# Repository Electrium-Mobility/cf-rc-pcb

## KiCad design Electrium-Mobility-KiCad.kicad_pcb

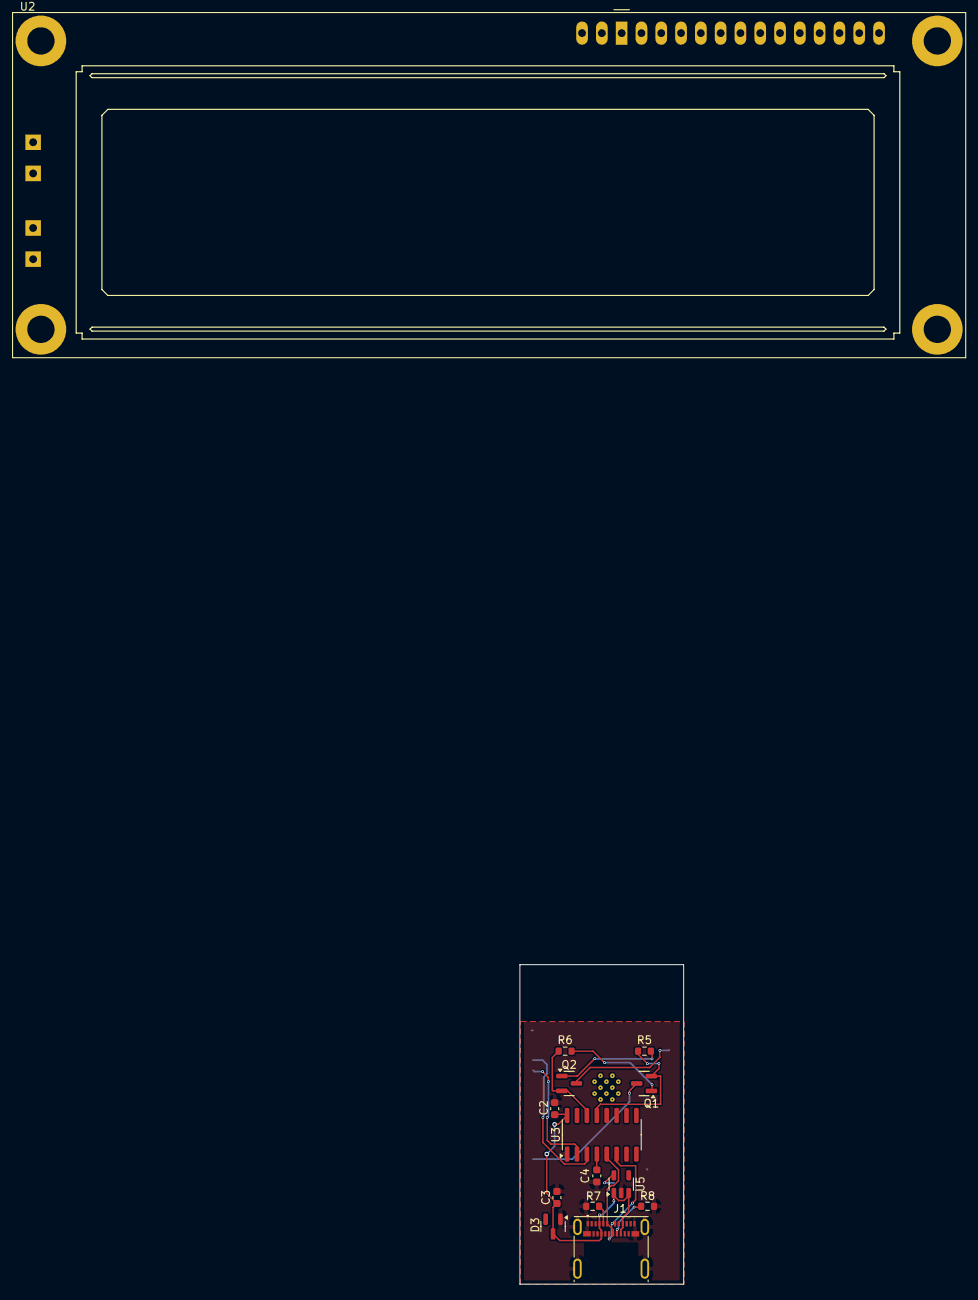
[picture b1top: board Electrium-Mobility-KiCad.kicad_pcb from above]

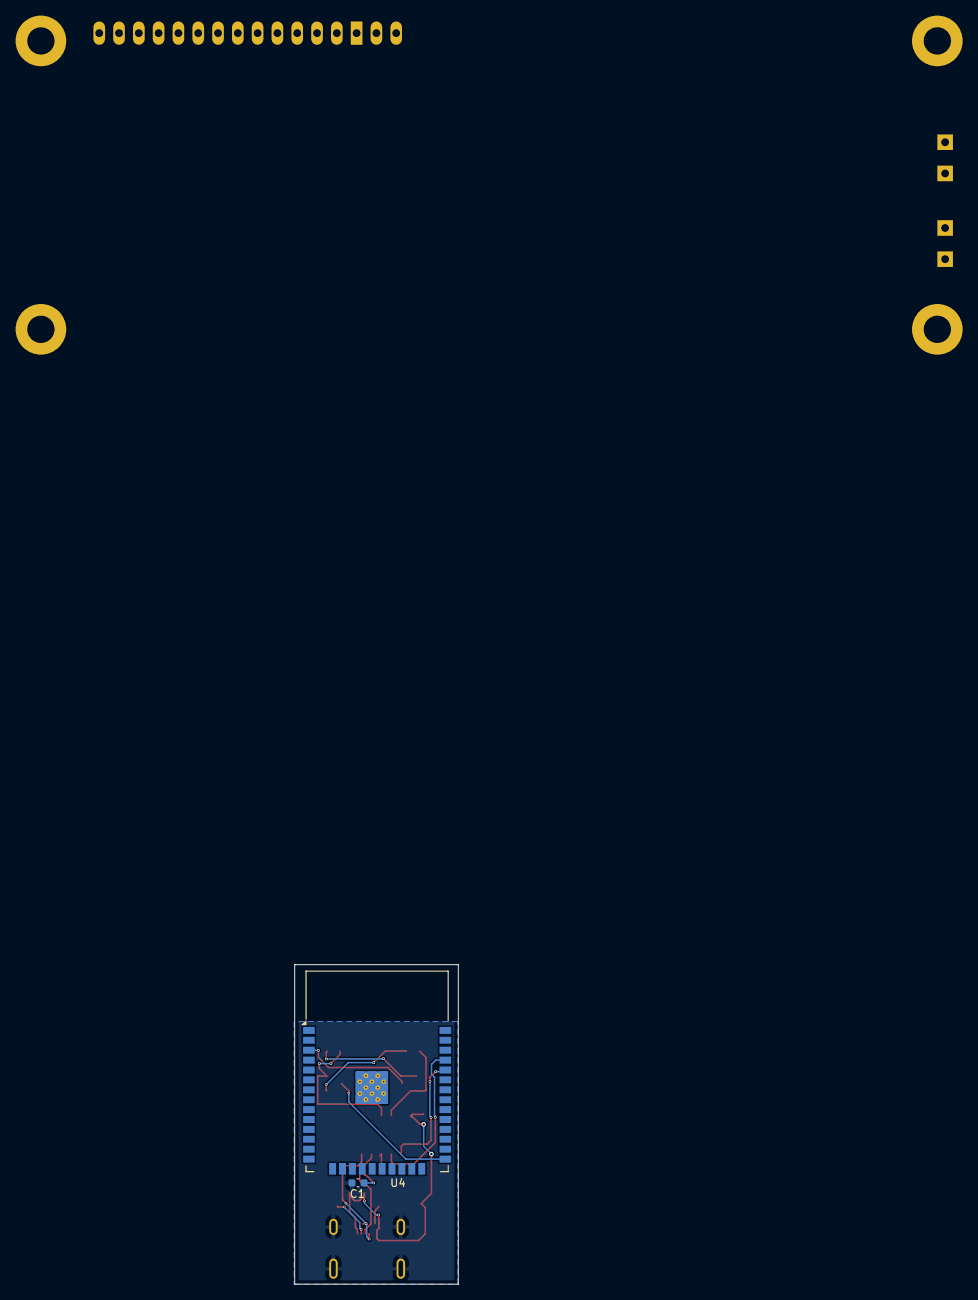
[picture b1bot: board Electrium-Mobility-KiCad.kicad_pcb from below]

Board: 2 copper layers, 21.0 x 41.0 mm, 16 parts (2 on the bottom side), 18 nets.

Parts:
C1: 10 uF; C_0603_1608Metric
C2, C3, C4: 100nF; C_0603_1608Metric
D3: D_Zener; SOT-23
J1: USB_C_Receptacle; USB_C_Receptacle_Molex_105450-0101
Q1, Q2: BC817; SOT-23
R5, R6: 10k; R_0603_1608Metric
R7, R8: 5.1k; R_0603_1608Metric
U2: LCD-016N002L
U3: CH340C; SOIC-16_3.9x9.9mm_P1.27mm
U4: ESP32-WROOM-32
U5: MIC5504-3.3YM5; SOT-23-5

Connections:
+3.3V: C1.1, U5.5 (VOUT)
+5V: C2.1, C3.1, D3.3 (K), J1.A4 (VBUS), J1.A9 (VBUS), J1.B4 (VBUS), J1.B9 (VBUS), U3.16 (VCC), U5.1 (VIN), U5.3 (EN)
/USB and Programmer/ESP_EN: Q2.3 (C), U4.3 (EN)
/USB and Programmer/ESP_IO0: Q1.3 (C), U4.25 (IO0)
/USB and Programmer/ESP_RX: U3.2 (TXD), U4.34 (RXD0/IO3)
/USB and Programmer/ESP_TX: U3.3 (RXD), U4.35 (TXD0/IO1)
/USB and Programmer/USB_D+: J1.A6 (D+), J1.B6 (D+), U3.5 (UD+)
/USB and Programmer/USB_D-: J1.A7 (D-), J1.B7 (D-), U3.6 (UD-)
GND: C1.2, C2.2, C3.2, C4.2, D3.1 (A), J1.A1 (GND), J1.A12 (GND), J1.B1 (GND), J1.B12 (GND), J1.S1 (SHIELD), R7.2, R8.2, U2.1 (VSS), U2.5 (R/~W), U2.16 (K), U2.K1, U2.K2, U3.1 (GND), U5.2 (GND)
unnamed: J1.A5 (CC1), R7.1
unnamed: J1.B5 (CC2), R8.1
unnamed: Q1.1 (B), R6.2
unnamed: Q1.2 (E), R5.1, U3.13 (~DTR)
unnamed: Q2.1 (B), R5.2
unnamed: Q2.2 (E), R6.1, U3.14 (~RTS)
unnamed: C4.1, U3.4 (V3)
unnamed: U4.1 (GND), U4.15 (GND), U4.38 (GND), U4.39 (GND)
VDD: U2.2 (VDD), U2.15 (A/VEE), U2.A1, U2.A2

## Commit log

2024-10-31 Added WIP files
2024-11-01 Added a schematic hierarcy
2024-11-01 Moved the motor into the relevant subschematic
2024-11-01 Added a test text
2024-11-15 progress
2024-11-15 pull down resistors included, don't seem necessary so double check
2024-11-15 might be updated pcb schematic?
2024-11-20 don't need pull down for RX and TX. Difficult to route D- and D+ with via's. Can you change line thickness?
2024-11-20 saved file again and committing to be sure
2024-11-21 One of the 5V is impossible to route. Would having a different type of USB-C connector help?
2024-11-21 i saved and close pcb layout, hopefully saved properly
2024-11-21 check connectivity for the ones I couldn't route, i think they're impossible
2024-11-22 Battery charger circuit
2024-11-22 Fix Schematic Signed-off-by: David Xu <131167198+DavidX787@users.noreply.github.com>
2024-11-26 This sbould be the final pcb layout, adjust pcb size and delete random lcd on there?
2024-11-27 final sizing
2024-11-29 the part tags are gone? opened incorrectly?
2024-11-29 names are fixed
2024-11-29 ground still not working
2024-11-29 save
